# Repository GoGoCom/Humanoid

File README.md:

# Humanoid

## Introduction

I built a humanoid robot using the ESP32. For robot control, I used the ESP32's BLE or WiFi functions. I utilized PLEN's motion data to capture the robot's movement data.

## Control in webPage using ESP32's BLE

After connecting to the robot via BLE on a web browser on a laptop or PC, you can directly operate the 16 joints or open a data file for a specific continuous movement and make it move. The movement file is borrowed from PLEN-Project( https://github.com/plenprojectcompany ) and can be converted for use, and you can also create movements directly using PLEN's [motion-editor](https://plen.jp/playground/motion-editor/).

## Blynk Tools

[Blynk](https://www.blynk.io/) is an excellent platform for solving IoT problems.It is the most powerful tool when you want to control something on the Internet, whether it is on mobile or PC.
By defining the required streams in the Blynk.Console and connecting them to components, you can exchange data over the network.
You must first sign up on https://blynk.cloud/dashboard/login  before you can use it.

After defining the device and setting up the development template through the Blynk console, find out the following three values and enter them at the beginning of the source code: BLYNK TEMPLATE ID, BLYNK TEMPLATE_NAME, and BLYNK AUTHTOKEN.

| define |
|-|
|#define BLYNK_TEMPLATE_ID  "XMgt6fqp4aXvb" |
|#define BLYNK_TEMPLATE_NAME  "Humanoid" |
|#define BLYNK_AUTH_TOKEN  "0f0ffASdldldleefeeXXiCNCvQT3Ff3H" |

### Blynk App / Display

## Library
| Library | version | description |
|-|-|-|
| Blynk | 1.3.2 | IoT |
| ESP8266 and ESP32 OLED driver foe SSSD1306 | 4.6.2 | display |
| ArduinoJson | 7.4.2 | motion datat parsing  |
| ESP32Servo | 3.0.9 | Servo motor  |

## Tool
| Tool | version | description |
|-|-|-|
| Autodesk Eagle | 9.6.2 | hardware |
| Arduino IDE | 2.3.7 | software |

## Acknowledgments

I would like to thank to every one, specially PLEN project team and Rui Santos of RandomNerdTutorials for their contributions.

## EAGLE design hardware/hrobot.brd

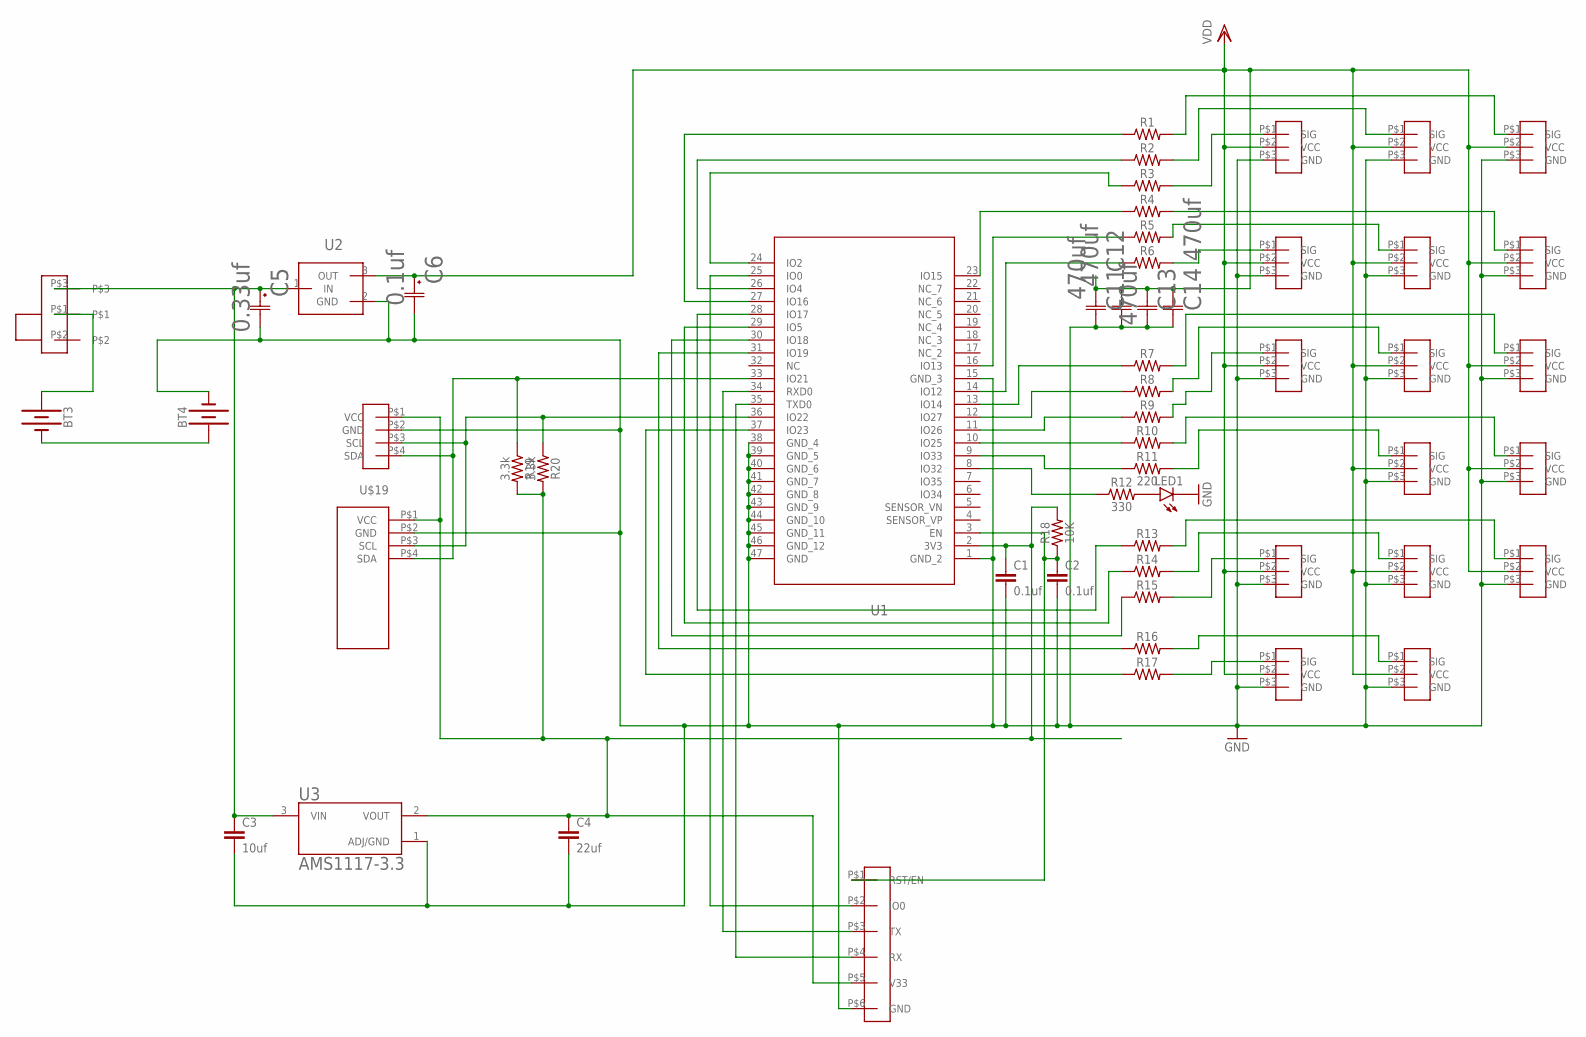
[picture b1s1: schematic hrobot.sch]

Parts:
BT3, BT4: BATTERY-18650; BATTERY_18650-HOLDER
C1, C2: 0.1uf; 0805
C3: 10uf; 0805
C4: 22uf; 0805
C5: 0.33uf; CAP_UWF_4X5P4_NCH
C6: 0.1uf; CAP_UZE_4X3P9_NCH
C11, C12, C13, C14: 470uf; CAP_J-V_8X10P5_RUB
LED1: LEDSML0805; SML0805
R1, R2, R3, R4, R5, R6, R7, R8, R9, R10, R13, R14, R15, R16, R17: 0805
R11: 220; 0805
R12: 330; 0805
R18: 10K; 0805
R19, R20: 3.3k; 0805
U1: ESP32-WROOM-32E_(4MB)ESP32�WROOM�32E_EXP; ESP32�WROOM�32E_EXP
U2: L7806; L7805FOOT
U3: AMS1117-3.3; SOT229P700X180-4N
U$1, U$2, U$3, U$5, U$6, U$7, U$8, U$9, U$10, U$11, U$12, U$13, U$14, U$15, U$16, U$17: SERVO; 3PINS
U$18: OLEDVCC; OLEPINS
U$19: GYRO; 4PINS
U$20: PWR3PINS
U$23: USBCOUT; 6PINS

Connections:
3V3: C1.1, C4.1, R18.2, R19.2, R20.2, U1.2 (3V3), U3.2 (VOUT), U$18.P$1 (VCC), U$19.P$1 (VCC), U$23.P$5 (V33)
GND: BT4.GND@1 (-), C1.2, C2.2, C3.2, C4.2, C5.2, C6.2, C11.2, C12.2, C13.2, C14.2, LED1.C, U1.1 (GND_2), U1.15 (GND_3), U1.38 (GND_4), U1.39 (GND_5), U1.40 (GND_6), U1.41 (GND_7), U1.42 (GND_8), U1.43 (GND_9), U1.44 (GND_10), U1.45 (GND_11), U1.46 (GND_12), U1.47 (GND), U2.2 (GND), U3.1 (ADJ/GND), U$1.P$3 (GND), U$2.P$3 (GND), U$3.P$3 (GND), U$5.P$3 (GND), U$6.P$3 (GND), U$7.P$3 (GND), U$8.P$3 (GND), U$9.P$3 (GND), U$10.P$3 (GND), U$11.P$3 (GND), U$12.P$3 (GND), U$13.P$3 (GND), U$14.P$3 (GND), U$15.P$3 (GND), U$16.P$3 (GND), U$17.P$3 (GND), U$18.P$2 (GND), U$19.P$2 (GND), U$23.P$6 (GND)
unnamed: BT3.GND@1 (-), BT4.PWR@1 (+)
unnamed: BT3.PWR@1 (+), U$20.P$1
unnamed: R3.2, U$1.P$1 (SIG)
unnamed: R2.2, U$7.P$1 (SIG)
unnamed: R1.2, U$13.P$1 (SIG)
unnamed: R6.2, U$2.P$1 (SIG)
unnamed: R5.2, U$8.P$1 (SIG)
unnamed: R4.2, U$14.P$1 (SIG)
unnamed: R9.2, U$3.P$1 (SIG)
unnamed: R8.2, U$9.P$1 (SIG)
unnamed: R7.2, U$15.P$1 (SIG)
unnamed: LED1.A, R12.2
unnamed: R11.2, U$10.P$1 (SIG)
unnamed: R10.2, U$16.P$1 (SIG)
unnamed: R15.2, U$5.P$1 (SIG)
unnamed: R14.2, U$11.P$1 (SIG)
unnamed: R13.2, U$17.P$1 (SIG)
unnamed: R17.2, U$6.P$1 (SIG)
unnamed: R16.2, U$12.P$1 (SIG)
unnamed: C3.1, C5.1, U2.1 (IN), U3.3 (VIN), U$20.P$3
unnamed: R16.1, U1.31 (IO19)
unnamed: R1.1, U1.27 (IO16)
unnamed: R2.1, U1.26 (IO4)
unnamed: C2.1, R18.1, U1.3 (EN), U$23.P$1 (RST/EN)
unnamed: R4.1, U1.23 (IO15)
unnamed: R5.1, U1.16 (IO13)
unnamed: R6.1, U1.14 (IO12)
unnamed: R17.1, U1.37 (IO23)
unnamed: R14.1, U1.29 (IO5)
unnamed: R15.1, U1.30 (IO18)
unnamed: R13.1, U1.28 (IO17)
unnamed: R19.1, U1.33 (IO21), U$18.P$4 (SDA), U$19.P$4 (SDA)
unnamed: R11.1, U1.9 (IO33)
unnamed: R10.1, U1.10 (IO25)
unnamed: R9.1, U1.11 (IO26)
unnamed: R8.1, U1.12 (IO27)
unnamed: R7.1, U1.13 (IO14)
unnamed: R20.1, U1.36 (IO22), U$18.P$3 (SCL), U$19.P$3 (SCL)
unnamed: R12.1, U1.8 (IO32)
unnamed: R3.1, U1.24 (IO2)
unnamed: U1.35 (TXD0), U$23.P$4 (RX)
unnamed: U1.34 (RXD0), U$23.P$3 (TX)
unnamed: U1.25 (IO0), U$23.P$2 (IO0)
VDD: C6.1, C11.1, C12.1, C13.1, C14.1, U2.3 (OUT), U$1.P$2 (VCC), U$2.P$2 (VCC), U$3.P$2 (VCC), U$5.P$2 (VCC), U$6.P$2 (VCC), U$7.P$2 (VCC), U$8.P$2 (VCC), U$9.P$2 (VCC), U$10.P$2 (VCC), U$11.P$2 (VCC), U$12.P$2 (VCC), U$13.P$2 (VCC), U$14.P$2 (VCC), U$15.P$2 (VCC), U$16.P$2 (VCC), U$17.P$2 (VCC)

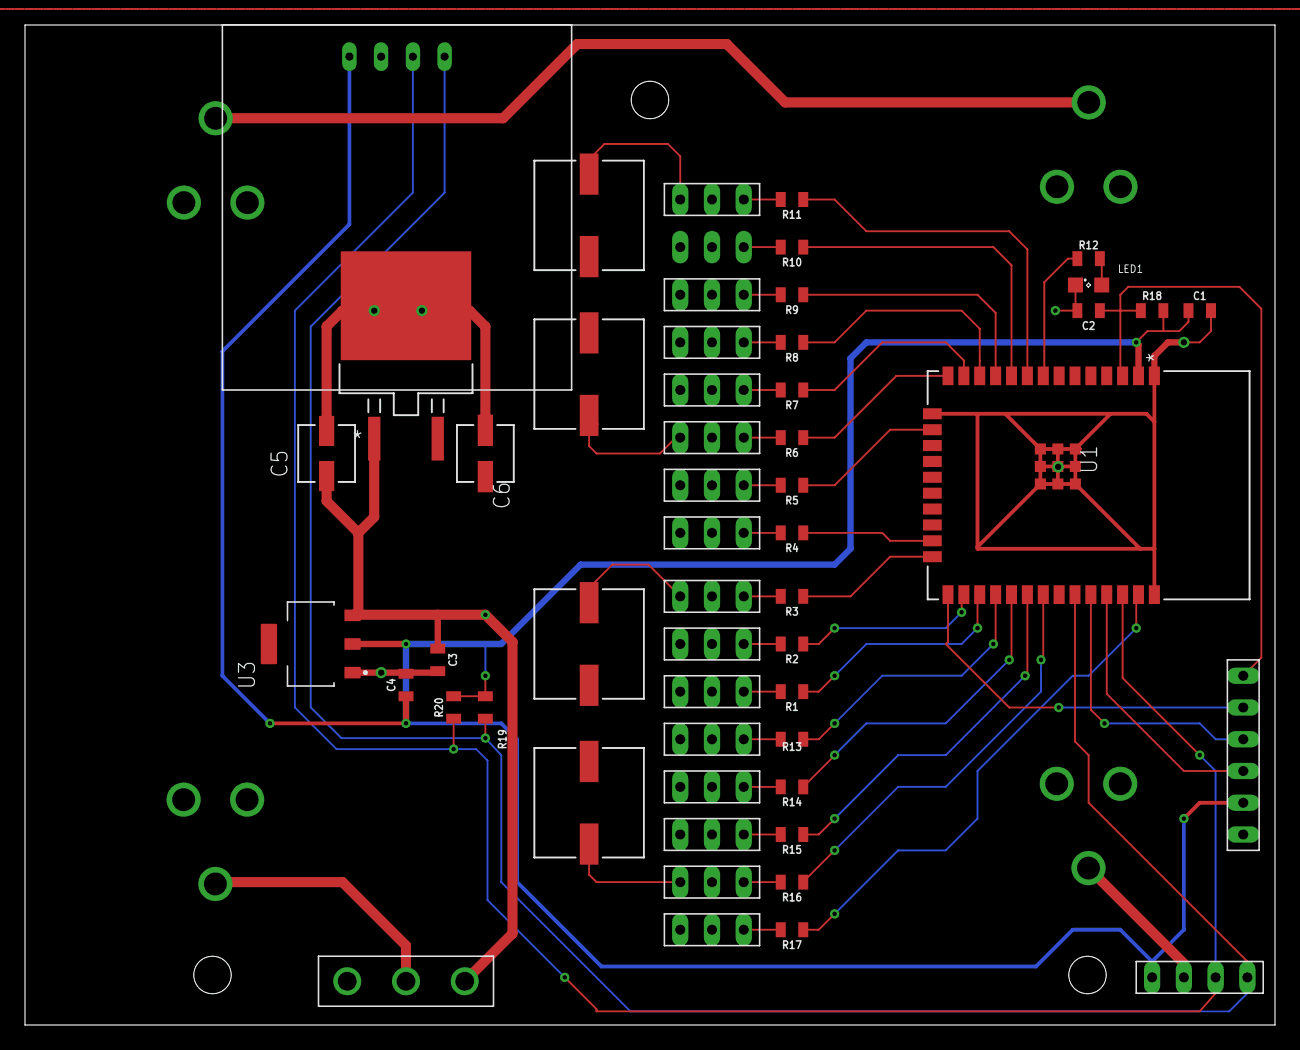
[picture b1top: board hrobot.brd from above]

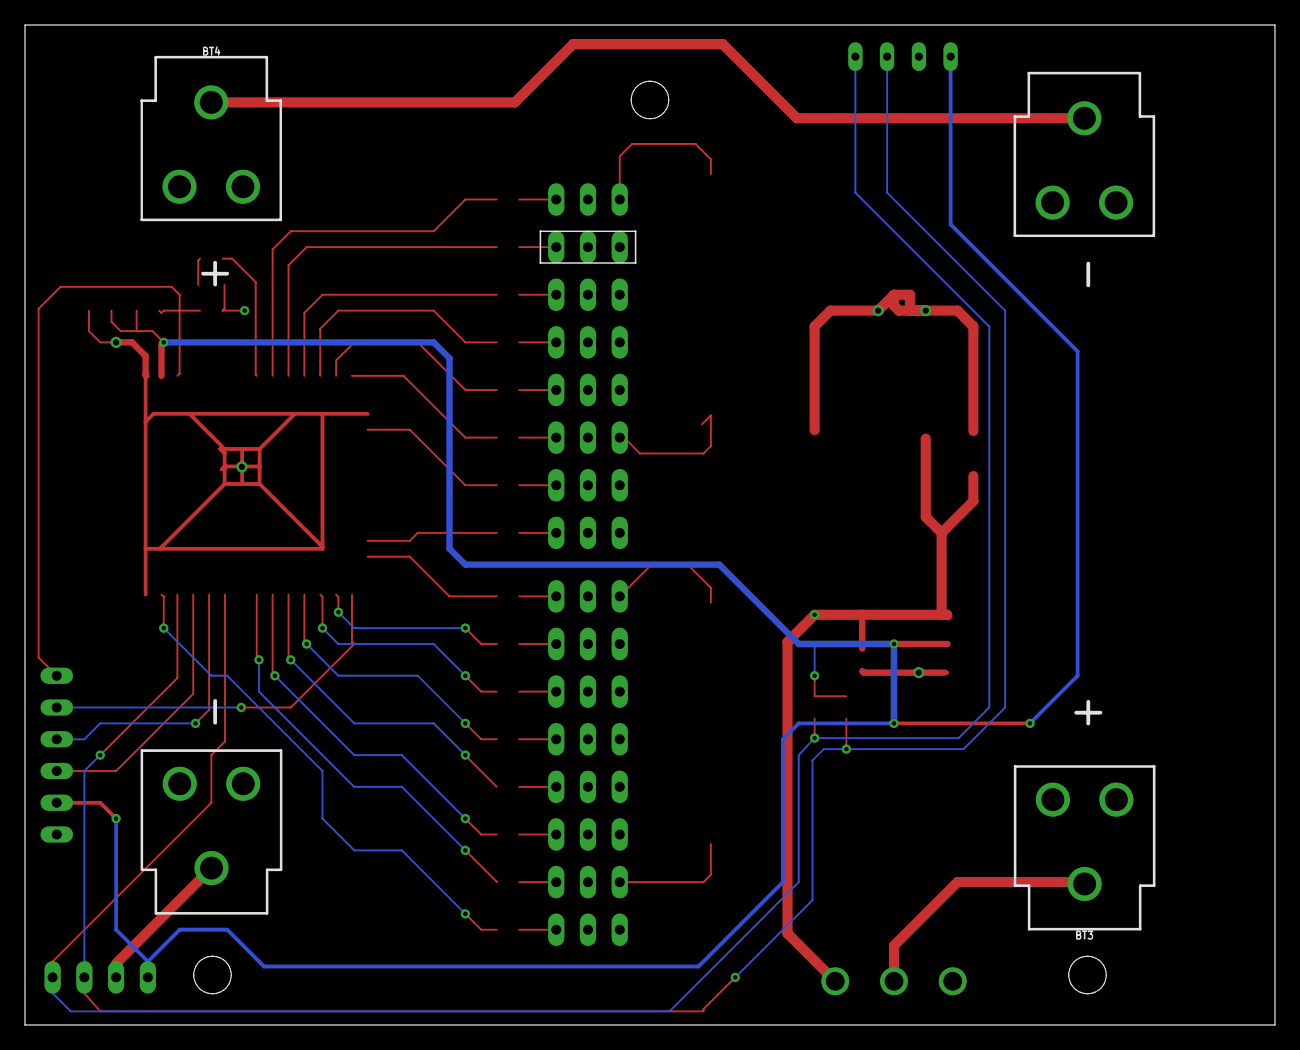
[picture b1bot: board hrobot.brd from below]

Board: 2 copper layers, 100.0 x 80.0 mm, 56 parts (3 on the bottom side), 46 nets.

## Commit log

2026-01-16 uploads
2026-01-16 upload

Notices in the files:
parts and their libraries:
SparkFun-Resistors: Licensing: Creative Commons ShareAlike 4.0 International - https://creativecommons.org/licenses/by-sa/4.0
COPYRIGHT: Copyright (C) 2024 Ultra Librarian. All rights reserved.
COPYRIGHT: Copyright (C) 2025 Ultra Librarian. All rights reserved.
